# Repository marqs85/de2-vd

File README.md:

DE2-vd
==============

DE2-vd is a video digitization add-on module for Altera DE2-115 FPGA development board. Together with DE2-115, it can be used in converting analog RGB/component video into digital format with very low processing latency. The system is mainly designed for using retro game consoles / home computers on modern displays.

The module is a prototype for a single-board digitization and scan converter system to be released in the future. Therefore, the current system is targeted for developers / hobbyists interested in FPGA design and video digitization - no in-depth documentation is currently provided.

Features
--------------
* detects and digitizes various video modes from 240p to 1280x1024 (and possibly higher with future updates)
* linedouble-support for 240p, 480i, 288p, 576i
* linetriple-support for 240p with 4 different sampling modes
* very low latency (less than 2 input scanlines)
* single-field "deinterlace" for 480i/576i: minimal latency overhead with decent image quality
* quick recover from input video mode change (e.g. 240p<->480i)
* all video processing done in RGB domain - no conversion to YCbCr
* multiple inputs supporting various formats
 * RGBS via SCART connector
 * RGBHV/RGBS via VGA connector
 * YPbPr/RGsB via 3xRCA connector
* Two possible output methods
 * full-range RGB output through HDMI
 * analog RGB output through VGA DAC
* emulated scanlines with configurable strength
* configurable mask for overscan area
* configurable horizontal sample rate (only limited by display support)
* fully open source: rtl, software and pcb design files all avaiable for modification

Required HW and SW
---------------------------------------------------
* Hardware
 * [Altera DE2-115 FPGA development board](http://www.terasic.com.tw/cgi-bin/page/archive.pl?Language=English&CategoryNo=139&No=502)
 * [HDMI Transmitter Daughter Card](http://www.terasic.com.tw/cgi-bin/page/archive.pl?Language=English&CategoryNo=66&No=582) (optional, for HDMI output)
 * DE2-vd [PCB](https://oshpark.com/shared_projects/yam1ykak) and [components](pcb/BOM_mouser.xls)
 * SMA and 2x20 ribbon cables between the boards (as short as possible)
 * 5V DC power supply (min. 1A, 1.3/4.5mm center positive)

* Software
 * [Altera Quartus II](http://dl.altera.com/?edition=web) (v 14.1 or higher - free Web edition available)
 * [Altera University Program IP](http://www.altera.com/education/univ/software/upds/unv-upds.html) (for on-board LCD character display)

Connection diagrams
------------------------------

DE2-vd module connections

DE2-115 board controls and connections

Build instructions
--------------------------
1. Edit rtl/output_sel.v.example to suit your setup, and save the modified file into rtl/output_sel.v
2. Load the project (videoproc.qpf) in Quartus II
3. Generate Qsys system files (Tools -> Qsys. Open sys.qsys -> Generate -> Generate HDL)
4. Generate the FPGA bitstream (Quartus window -> Processing -> Start Compilation)
5. Program the bitstream into the FPGA using either JTAG (volatile/.sof) or AS programming (nonvolatile/.pof) method

Usage
--------------------------
Before turning on the power, set jumpers JP7 and JP8 on the DE2-115 development board into 3.3V position. After programming the FPGA, the character LCD and 7-segment LEDs should display "OSSC" if the connection between the boards is operational.

### Input selection ###

Active input and format can be selected by using the 3 leftmost push-buttons on the board (see connection diagram). The inputs and corresponding connectors and formats are listed in the following table. The format within one input can be switched by pressing the same input button again.

Input | Connector | Format
------| ----------|-------
AV1 | SCART | RGBS (csync or cvbs as sync)
AV2 | VGA | RGBHV
 |  | RGBS (csync connected to pin 13)
AV3 | 3xRCA | YPbPr
 | | RGsB

### Line multiplier configuration ###

With SD video input, the line multiplier is activated in order to generate an output which is accepted by the target display. By default, the system uses linedouble and a horizontal sampling rate which results to 720 active pixels (720x480 with 60Hz, 720x576 with 50Hz). This is a standard mode which is compatible with basically all HDMI-enabled displays.

With 240p input, it is possible to improve output quality by enabling linetripler (L3_ENABLE=1) and selecting a suitable sampling mode (L3_MODE). This allows sampling the input video with a rate which matches the rate of the DAC generating the video, or alternatively with significant oversampling. Moreover, the output resolution (1280x720) is closer to the native resolution of modern displays, resulting to less scaling. There features reduce the softness resulting from inoptimal sampling and/or scaling. The sampling modes are as follows:

L3_MODE[1:0] | Number | Description
------- | ------------|------------
00 | 0 | Input sampled at full 1280 horizontal, resulting to 1280x720 effective area. Generic oversampling mode for 16:9 video.
01 | 1 | Input sampled at 960 horizontal, resulting to 960x720 effective area. Generic oversampling mode for 4:3 video.
10 | 2 | Input sampled at 320 horizontal, multiplied by 3 in horizontal direction resulting to 960x720 effective area. A mode suitable for 320x240 input, e.g. PSX, N64.
11 | 3 | Input sampled at 256 horizontal, multiplied by 4 in horizontal direction resulting to 1024x720 effective area. A mode suitable for 256x240 input, e.g. SNES, MD.

NOTE: the 1280x720 mode outputted by linetripler does not match the standardized 1280x720 mode and is not guarateed to work correctly on all displays.

### Scanlines ###

Emulated scanlines can be enabled with SCANLINES_ENABLE-switch, and their strength is adjusted by SCANLINE_STR[2:0]. Scanlines are active every other output line with linedouble/bare digitize, and every third output line with linetriple.

### Border masking ###

Up to 15 pixels of input video's borders can be masked with black bars in horizontal and vertical direction via H_MASK[3:0] and V_MASK[3:0] switches.

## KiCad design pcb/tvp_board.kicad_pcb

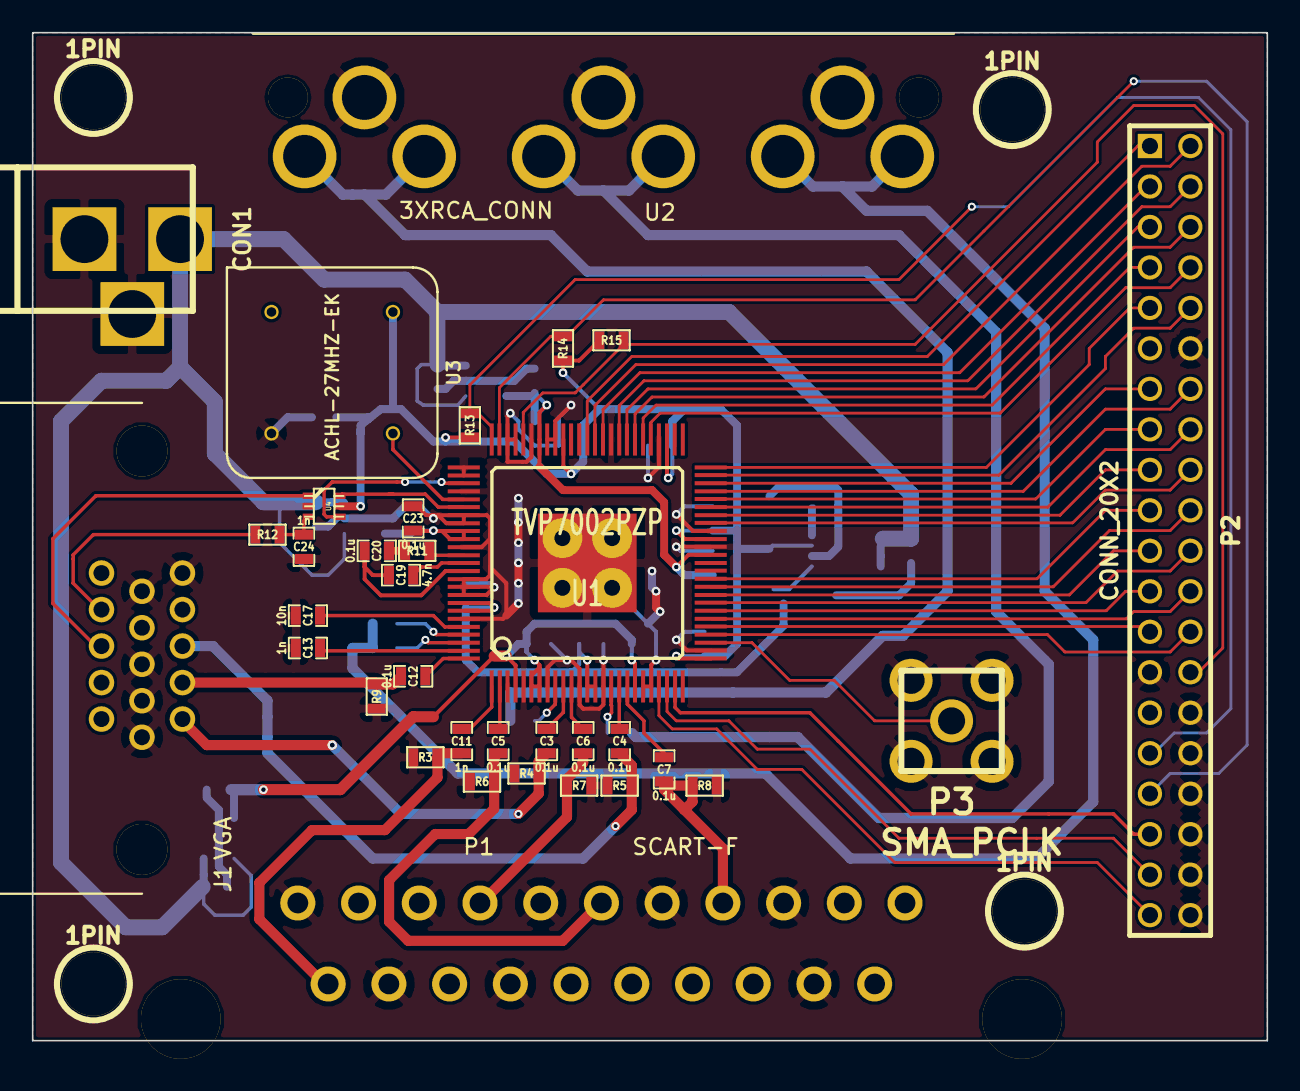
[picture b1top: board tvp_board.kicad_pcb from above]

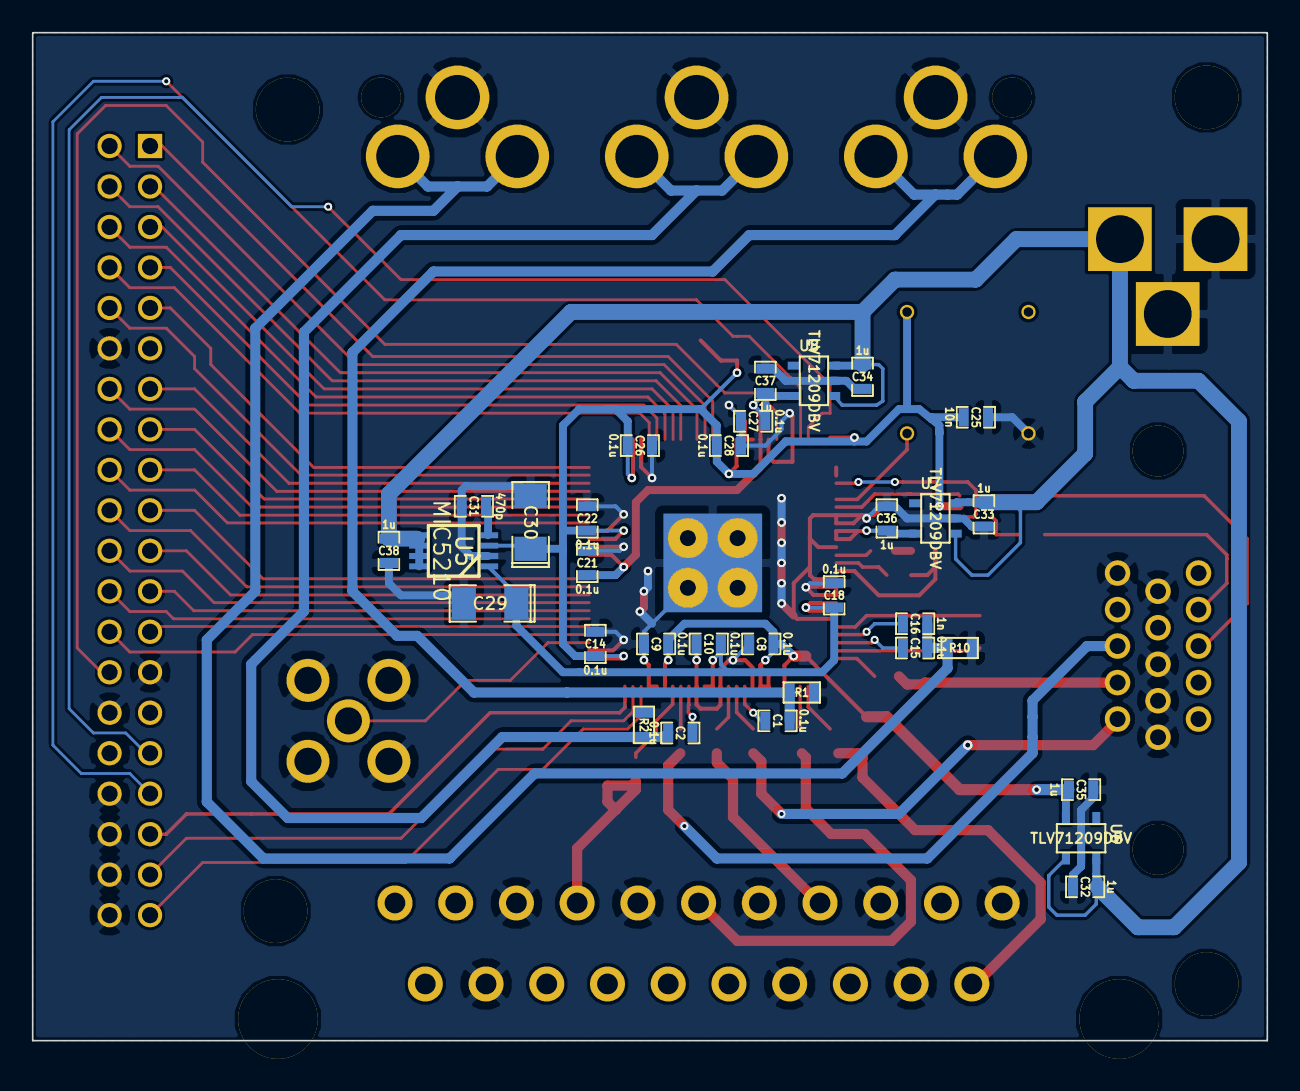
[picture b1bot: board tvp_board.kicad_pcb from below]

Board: 2 copper layers, 77.5 x 63.2 mm, 70 parts (32 on the bottom side), 72 nets.

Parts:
1PIN, 1PIN#2, 1PIN#3, 1PIN#4: P***; 1pin
C1, C2, C3, C4, C5, C6, C7, C8, C9, C10, C12, C14, C15, C18, C20, C21, C22, C23, C26, C27, C28: 0.1u; SM0603_Capa
C11, C13, C16, C24: 1n; SM0603_Capa
C17, C25: 10n; SM0603_Capa
C19: 4.7n; SM0603_Capa
C29, C30: 2.2u; SM1206POL
C31: 470p; SM0603_Capa
C32, C33, C34, C35, C36, C37, C38: 1u; SM0603_Capa
CON1: 5VDC_IN; BARREL_JACK_roundconn
J1: VGA; VGA_CONN
P1: SCART-F; SCART_CONN
P2: CONN_20X2; PIN_ARRAY_20X2
P3: SMA_PCLK; SMA_CONN
R1, R2, R3, R4, R5, R6, R7, R8, R9, R10: 75; SM0603
R11: 1.5k; SM0603
R12: 330; SM0603
R13, R14, R15: 2.2k; SM0603
U1: TVP7002PZP; TQFP_100-thermal
U2: 3XRCA_CONN; 3xRCA_CONN
U3: ACHL-27MHZ-EK; ACHL-24
U4: SN74LVC2G17; sc70-6
U5: MIC5210; MSOP_8
U6, U7, U8: TLV71209DBV; SOT23-5

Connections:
/A33VDD: C10.1, C18.2, C29.1, U1.13, U1.14, U1.93, U1.94, U5.1
/AVDD: C8.1, C9.1, C35.1, U1.4, U1.6, U1.7, U1.19, U6.5
/B_0: P2.19, U1.36
/B_1: P2.20, U1.35
/B_2: P2.21, U1.34
/B_3: P2.22, U1.33
/B_4: P2.23, U1.32
/B_5: P2.24, U1.31
/B_6: P2.25, U1.30
/B_7: P2.26, U1.29
/CLK27: U1.80, U3.5
/DVDD: C21.1, C27.1, C37.1, U1.39, U1.69, U8.5
/FIDOUT: P2.39, U1.22
/G_0: P2.9, U1.50
/G_1: P2.10, U1.49
/G_2: P2.13, U1.48
/G_3: P2.14, U1.47
/G_4: P2.15, U1.46
/G_5: P2.16, U1.45
/G_6: P2.17, U1.44
/G_7: P2.18, U1.43
/HSOUT: P2.35, U1.24
/IOVDD: C14.1, C22.1, C25.1, C26.1, C28.1, C30.1, R13.2, R14.1, R15.2, U1.26, U1.41, U1.53, U1.66, U3.8, U4.5, U5.3
/PCLK: P3.1, U1.28
/PLL_VDD: C23.1, C36.1, U1.84, U1.85, U7.5
/RESET: P2.28, R15.1, U1.71
/RGB1_B: C7.1, P1.7, R8.1
/RGB1_G: C5.1, P1.11, R6.1
/RGB1_R: C6.1, P1.15, R7.1
/RGB1_S: C11.1, P1.20, R3.1
/RGB2_B: C4.1, J1.3, R5.1
/RGB2_G: C12.1, J1.2, R9.1
/RGB2_HS: J1.13, U4.1
/RGB2_HS_B: U1.81, U4.6
/RGB2_R: C3.1, J1.1, R4.1
/RGB2_VS: J1.14, R12.2
/RGB2_VS_B: U1.78, U4.4
/RGB3_B: C2.1, R2.1, U2.2
/RGB3_G: C15.1, C16.1, R10.2, U2.1
/RGB3_R: C1.1, R1.1, U2.3
/R_0: P2.1, U1.63
/R_1: P2.2, U1.62
/R_2: P2.3, U1.61
/R_3: P2.4, U1.59
/R_4: P2.5, U1.58
/R_5: P2.6, U1.57
/R_6: P2.7, U1.56
/R_7: P2.8, U1.55
/SCL: P2.33, R14.2, U1.74
/SDA: P2.31, R13.1, U1.75
/VSOUT: P2.37, U1.23
GND: C8.2, C9.2, C10.2, C13.1, C14.2, C17.1, C18.1, C21.2, C22.2, C23.2, C24.2, C25.2, C26.2, C27.2, C28.2, C29.2, C30.2, C31.2, C32.2, C33.2, C34.2, C35.2, C36.2, C37.2, C38.2, CON1.2, CON1.3, J1.5, J1.6, J1.7, J1.8, J1.10, P1.4, P1.5, P1.9, P1.13, P1.14, P1.17, P1.18, P1.21, P2.12, P2.27, P2.30, P2.32, P2.34, P2.36, P2.38, P2.40, P3.2, R1.2, R2.2, R3.2, R4.2, R5.2, R6.2, R7.2, R8.2, R9.2, R10.1, U1.3, U1.5, U1.8, U1.12, U1.15, U1.20, U1.21, U1.27, U1.40, U1.42, U1.54, U1.60, U1.67, U1.68, U1.70, U1.72, U1.73, U1.76, U1.77, U1.79, U1.82, U1.83, U1.86, U1.90, U1.91, U1.92, U1.95, U2.4, U3.4, U4.2, U5.2, U6.2, U7.2, U8.2
unnamed: C24.1, R12.1, U4.3
unnamed: R11.2, U1.87
unnamed: C19.2, C20.1, U1.89
unnamed: C20.2, R11.1
unnamed: C19.1, U1.88
unnamed: C4.2, U1.17
unnamed: C5.2, U1.2
unnamed: C2.2, U1.16
unnamed: C7.2, U1.18
unnamed: C1.2, U1.9
unnamed: C3.2, U1.10
unnamed: C6.2, U1.11
unnamed: C17.2, U1.96
unnamed: C15.2, U1.98
unnamed: C12.2, U1.100
unnamed: C32.1, C33.1, C34.1, C38.1, CON1.1, U5.5, U5.6, U5.7, U5.8, U6.1, U6.3, U7.1, U7.3, U8.1, U8.3
unnamed: C16.2, U1.97
unnamed: C13.2, U1.99
unnamed: C11.2, U1.1
unnamed: C31.1, U5.4

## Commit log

2015-02-16 First public version.
2015-04-07 pcb: fix regulator names and library paths sys: add hw support for sd card and flash controller sys: fix IO definitions sys: sw: reduce code size
2017-04-16 - Fixed >25Mhz clock frequency for Altera serial controller - Update IPs to Quartus 16.1
2017-04-17 add updated files for fw 0.28
